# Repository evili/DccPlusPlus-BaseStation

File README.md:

# What's this fork of DCC++
### Please, do not use this fork of DCC++. This is pre-Alpha concept.
Visit and use the real original
[DCC++ BaseStation](https://github.com/DccPlusPlus/BaseStation)

For more info on the idea and intention of this fork, see [./Railcom.md]

What’s DCC++
------------

DCC++ is an open-source hardware and software system for the operation of DCC-equipped model railroads.

The system consists of two parts, the DCC++ Base Station and the DCC++ Controller.

The DCC++ Base Station consists of an Arduino micro controller fitted with an Arduino Motor Shield that can be connected directly to the tracks of a model railroad.

The DCC++ Controller provides operators with a customizable GUI to control their model railroad.  It is written in Java using the Processing graphics library and IDE and communicates with the DCC++ Base Station via a standard serial connection over a USB cable or wireless over BlueTooth.

What’s in this Repository
-------------------------

This repository, BaseStation-Uno, contains a complete DCC++ Base Station sketch designed for compiling and uploading into an Arduino Uno.  All sketch files are in the folder named DCCpp_Uno. More information about the sketch can be found in the included PDF file.

To utilize this sketch, simply download a zip file of this repository and open the file DCCpp_Uno.ino within the DCCpp_Uno folder using your Arduino IDE.  Please do not rename the folder containing the sketch code, nor add any files to that folder.  The Arduino IDE relies on the structure and name of the folder to properly display and compile the code.

The latest production release of the Master branch is 1.2.1:

* Supports both the Arduino Uno and Arduino Mega
* Built-in configuration for both the original Arduino Motor Shield as well as a Pololu MC33926 Motor Shield
* Built-in configuration and support of Ethernet Shields (for use with Mega only)

For more information on the overall DCC++ system, please follow the links in the PDF file.

Detailed diagrams showing pin mappings and required jumpers for the Motor Shields can be found in the Documentation Repository

The Master branch contains all of the Base Station functionality showed in the DCC++ YouTube channel with the exception of 2 layout-specific modules:

* Control for an RGB LED Light Strip using pins 44, 45, and 46 on the Mega
* An embedded AutoPilot routine that randomly selects a train to run through the entire layout, after which it is brought back into its original siding and the the patterns repeats with another randomly-selected train.  This is the AutoPilot routine showed on the DCC++ YouTube channel.  It does not require any computer, not DCC++ Controller to be running (DCC++ Controller contains a much more complicated 3-train Auto Pilot mode, also as shown on the DCC++ YouTube channel).

Since these modules are very layout-specififc, they are not included in the Master branch.  However, they are included in the Development branch.  Please feel free to download and copy any relevant code to customize your own version of DCC++ Base Station.

-December 27, 2015

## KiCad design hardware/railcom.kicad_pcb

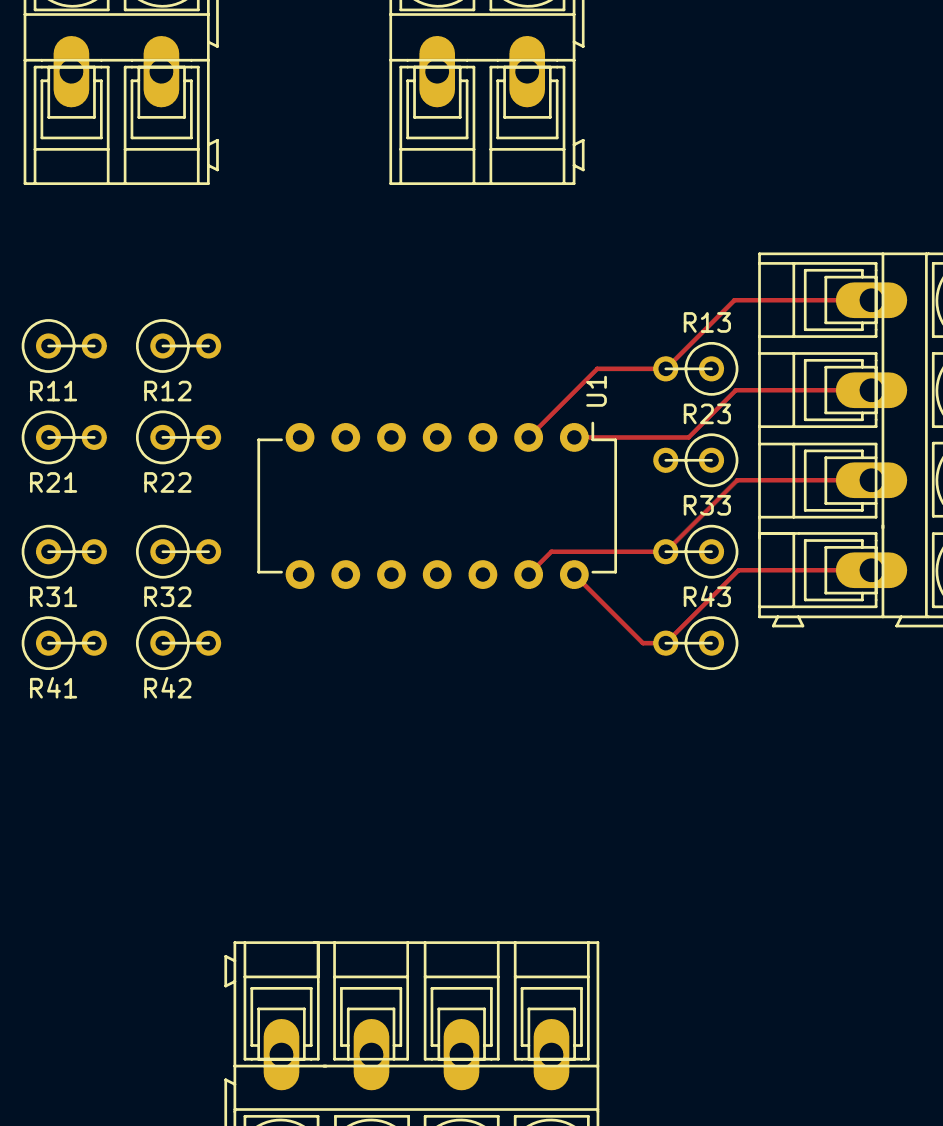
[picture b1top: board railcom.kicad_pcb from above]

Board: 2 copper layers, 17 parts (0 on the bottom side), 15 nets.

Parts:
P1, P2: CONN_01X04; AK300-4
P3, P4: CONN_01X02; AK300-2
R11, R21, R31, R41: 12K; R1
R12, R22, R32, R42: 1K; R1
R13, R23, R33, R43: 5K; R1
U1: LM339; DIP-14_W7.62mm

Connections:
+5V: P4.1, R13.1, R23.1, R33.1, R43.1
+12V: P3.1, R11.1, R21.1, R31.1, R41.1, U1.3
GND: P3.2, P4.2, R12.2, R22.2, R32.2, R42.2, U1.12
unnamed: P1.1, U1.4
unnamed: P1.2, U1.6
unnamed: P1.3, U1.10
unnamed: P1.4, U1.8
unnamed: P2.1, R13.2, U1.2
unnamed: P2.2, R23.2, U1.1
unnamed: P2.3, R33.2, U1.13
unnamed: P2.4, R43.2, U1.14
unnamed: R11.2, R12.1, U1.5
unnamed: R21.2, R22.1, U1.7
unnamed: R31.2, R32.1, U1.11
unnamed: R41.2, R42.1, U1.9

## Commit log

2016-05-04 Introduce railcom cutout
2016-05-05 Inserted cutout in ISR routine. Does nothing else.
2017-02-23 Add prototype schema
